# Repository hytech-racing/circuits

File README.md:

# circuits
Circuit design for the 2015-2016 car
## Getting Started
1. Get access to Google Drive folder
2. Download [Eagle CAD](http://www.cadsoftusa.com/download-eagle/)
3. Download vehicle electrical diagram from Google Drive: ***Hytech Main Folder/Subteam Files/Electrical/Wiring Diagram/***
4. Download EAGLE Hytech library from Google Drive: ***Hytech Main Folder/Subteam Files/Electrical/HyTech 2016.lbr***

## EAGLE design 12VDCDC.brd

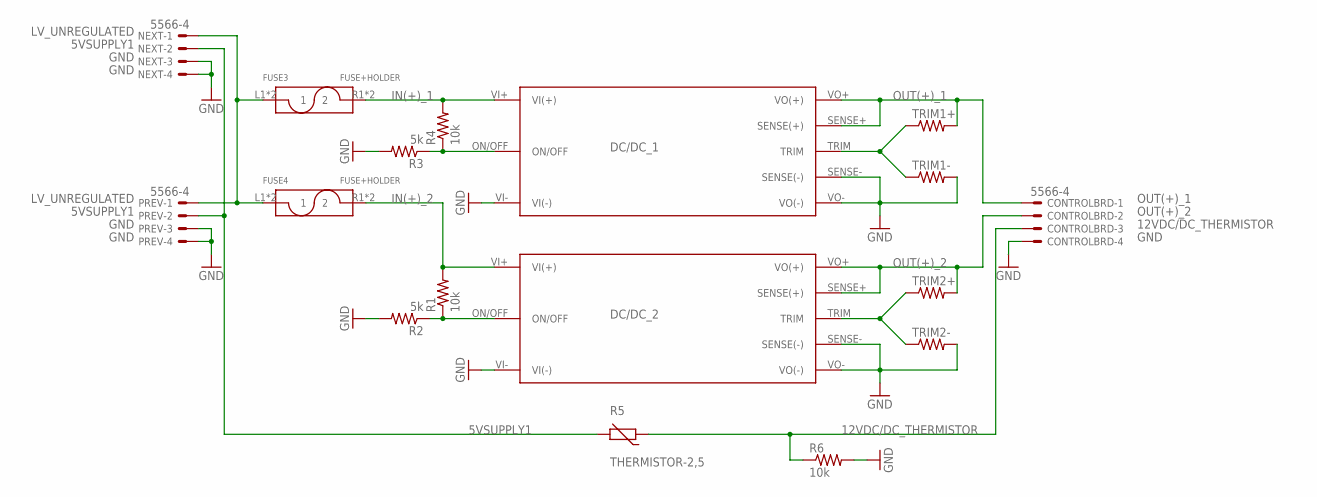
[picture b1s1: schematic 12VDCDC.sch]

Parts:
CONTROLBRD: 5566-4
DC/DC_1, DC/DC_2: DC/DC-EIGHTH_BRICKEHHD006A0B41-HZ; DC/DC-EIGHTH_BRICK
FUSE3, FUSE4: FUSE+HOLDER; FUSE-HOLDER
NEXT: 5566-4
PREV: 5566-4
R1, R4, R6: 10k; AXIAL-0.3
R2, R3: 5k; AXIAL-0.3
R5: THERMISTOR-2,5; RS-2,5
TRIM1+, TRIM1-, TRIM2+, TRIM2-: RESISTORPTH-1/4W; AXIAL-0.4

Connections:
5VSUPPLY1: NEXT.2, PREV.2, R5.2
12VDC/DC_THERMISTOR: CONTROLBRD.3, R5.1, R6.P$1 (1)
GND: CONTROLBRD.4, DC/DC_1.SENSE- (SENSE(-)), DC/DC_1.VI- (VI(-)), DC/DC_1.VO- (VO(-)), DC/DC_2.SENSE- (SENSE(-)), DC/DC_2.VI- (VI(-)), DC/DC_2.VO- (VO(-)), NEXT.3, NEXT.4, PREV.3, PREV.4, R2.P$2 (2), R3.P$2 (2), R6.P$2 (2), TRIM1-.P$2 (2), TRIM2-.P$2 (2)
IN(+)_1: DC/DC_1.VI+ (VI(+)), FUSE3.R1 (2), FUSE3.R2 (2), R4.P$2 (2)
IN(+)_2: DC/DC_2.VI+ (VI(+)), FUSE4.R1 (2), FUSE4.R2 (2), R1.P$2 (2)
LV_UNREGULATED: FUSE3.L1 (1), FUSE3.L2 (1), FUSE4.L1 (1), FUSE4.L2 (1), NEXT.1, PREV.1
unnamed: DC/DC_1.TRIM, TRIM1+.P$1 (1), TRIM1-.P$1 (1)
unnamed: DC/DC_2.ON/OFF, R1.P$1 (1), R2.P$1 (1)
unnamed: DC/DC_1.ON/OFF, R3.P$1 (1), R4.P$1 (1)
unnamed: DC/DC_2.TRIM, TRIM2+.P$1 (1), TRIM2-.P$1 (1)
OUT(+)_1: CONTROLBRD.1, DC/DC_1.SENSE+ (SENSE(+)), DC/DC_1.VO+ (VO(+)), TRIM1+.P$2 (2)
OUT(+)_2: CONTROLBRD.2, DC/DC_2.SENSE+ (SENSE(+)), DC/DC_2.VO+ (VO(+)), TRIM2+.P$2 (2)

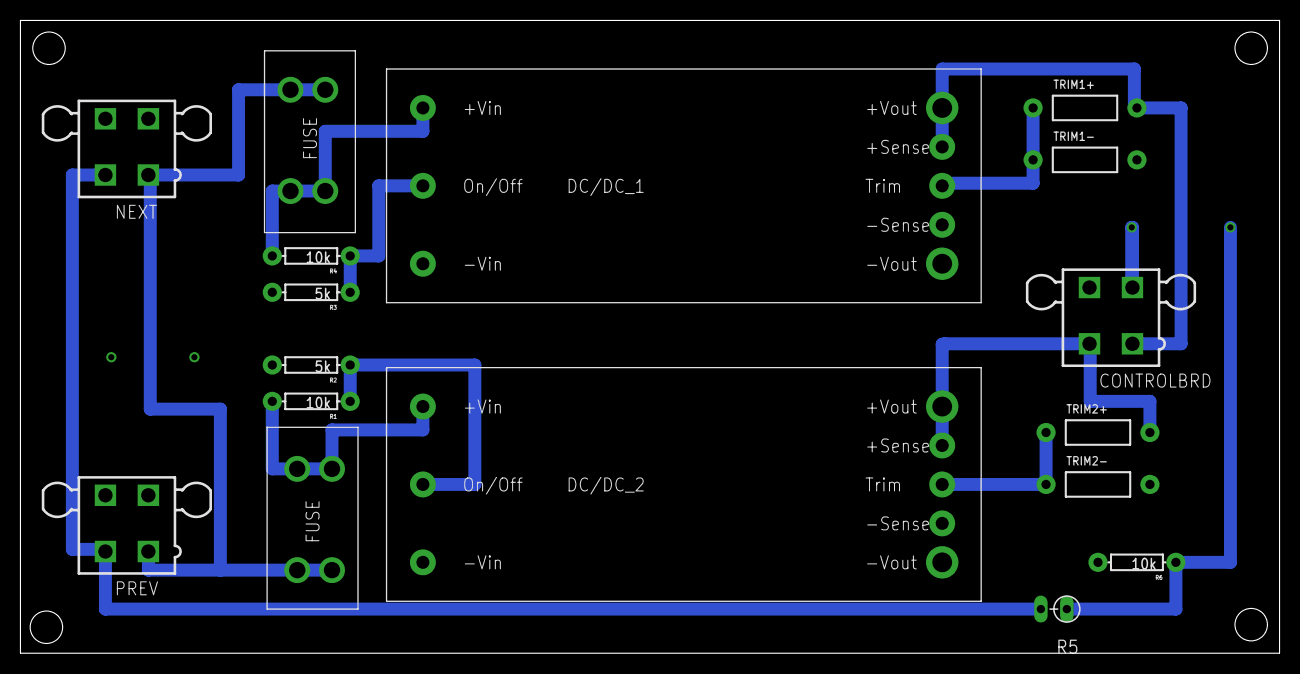
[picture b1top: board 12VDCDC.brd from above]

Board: 2 copper layers, 123.2 x 61.9 mm, 17 parts (0 on the bottom side), 12 nets.

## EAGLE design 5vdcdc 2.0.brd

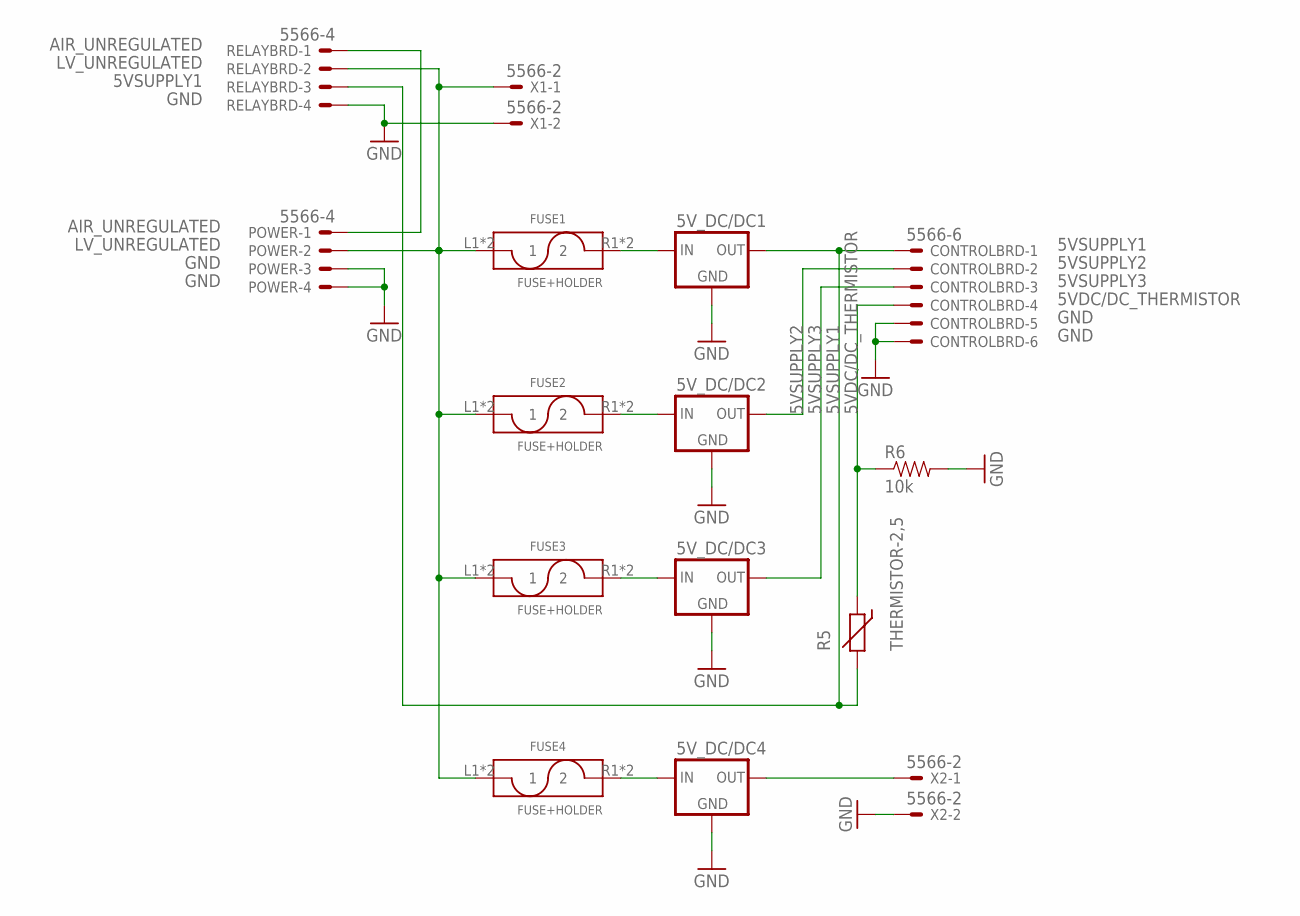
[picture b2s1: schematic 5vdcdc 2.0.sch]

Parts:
5V_DC/DC1, 5V_DC/DC2, 5V_DC/DC3, 5V_DC/DC4: 5V_REGULATORLINEAR; TO-220-SINK
CONTROLBRD: 5566-6
FUSE1, FUSE2, FUSE3, FUSE4: FUSE+HOLDER; FUSE-HOLDER
POWER: 5566-4
R5: THERMISTOR-2,5; RS-2,5
R6: 10k; AXIAL-0.3
RELAYBRD: 5566-4
X1, X2: 5566-2

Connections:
5VDC/DC_THERMISTOR: CONTROLBRD.4, R5.1, R6.P$1 (1)
5VSUPPLY1: 5V_DC/DC1.3 (OUT), CONTROLBRD.1, R5.2, RELAYBRD.3
5VSUPPLY2: 5V_DC/DC2.3 (OUT), CONTROLBRD.2
5VSUPPLY3: 5V_DC/DC3.3 (OUT), CONTROLBRD.3
AIR_UNREGULATED: POWER.1, RELAYBRD.1
GND: 5V_DC/DC1.2 (GND), 5V_DC/DC2.2 (GND), 5V_DC/DC3.2 (GND), 5V_DC/DC4.2 (GND), CONTROLBRD.5, CONTROLBRD.6, POWER.3, POWER.4, R6.P$2 (2), RELAYBRD.4, X1.2, X2.2
LV_UNREGULATED: FUSE1.L1 (1), FUSE1.L2 (1), FUSE2.L1 (1), FUSE2.L2 (1), FUSE3.L1 (1), FUSE3.L2 (1), FUSE4.L1 (1), FUSE4.L2 (1), POWER.2, RELAYBRD.2, X1.1
unnamed: 5V_DC/DC1.1 (IN), FUSE1.R1 (2), FUSE1.R2 (2)
unnamed: 5V_DC/DC2.1 (IN), FUSE2.R1 (2), FUSE2.R2 (2)
unnamed: 5V_DC/DC3.1 (IN), FUSE3.R1 (2), FUSE3.R2 (2)
unnamed: 5V_DC/DC4.1 (IN), FUSE4.R1 (2), FUSE4.R2 (2)
unnamed: 5V_DC/DC4.3 (OUT), X2.1

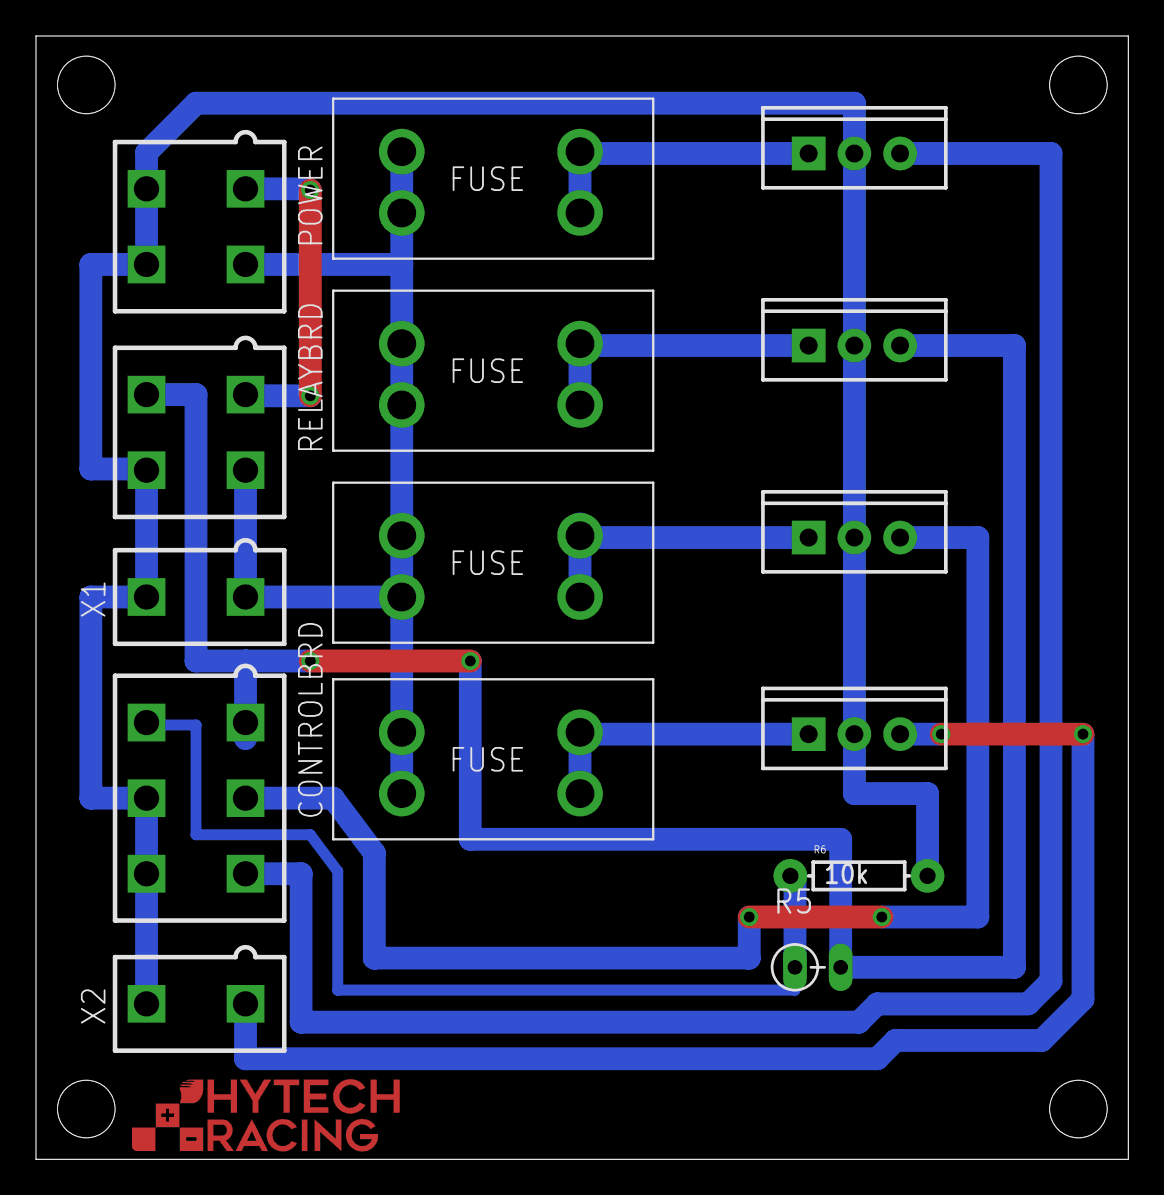
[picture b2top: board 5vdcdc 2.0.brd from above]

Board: 2 copper layers, 60.7 x 62.4 mm, 15 parts (0 on the bottom side), 12 nets.

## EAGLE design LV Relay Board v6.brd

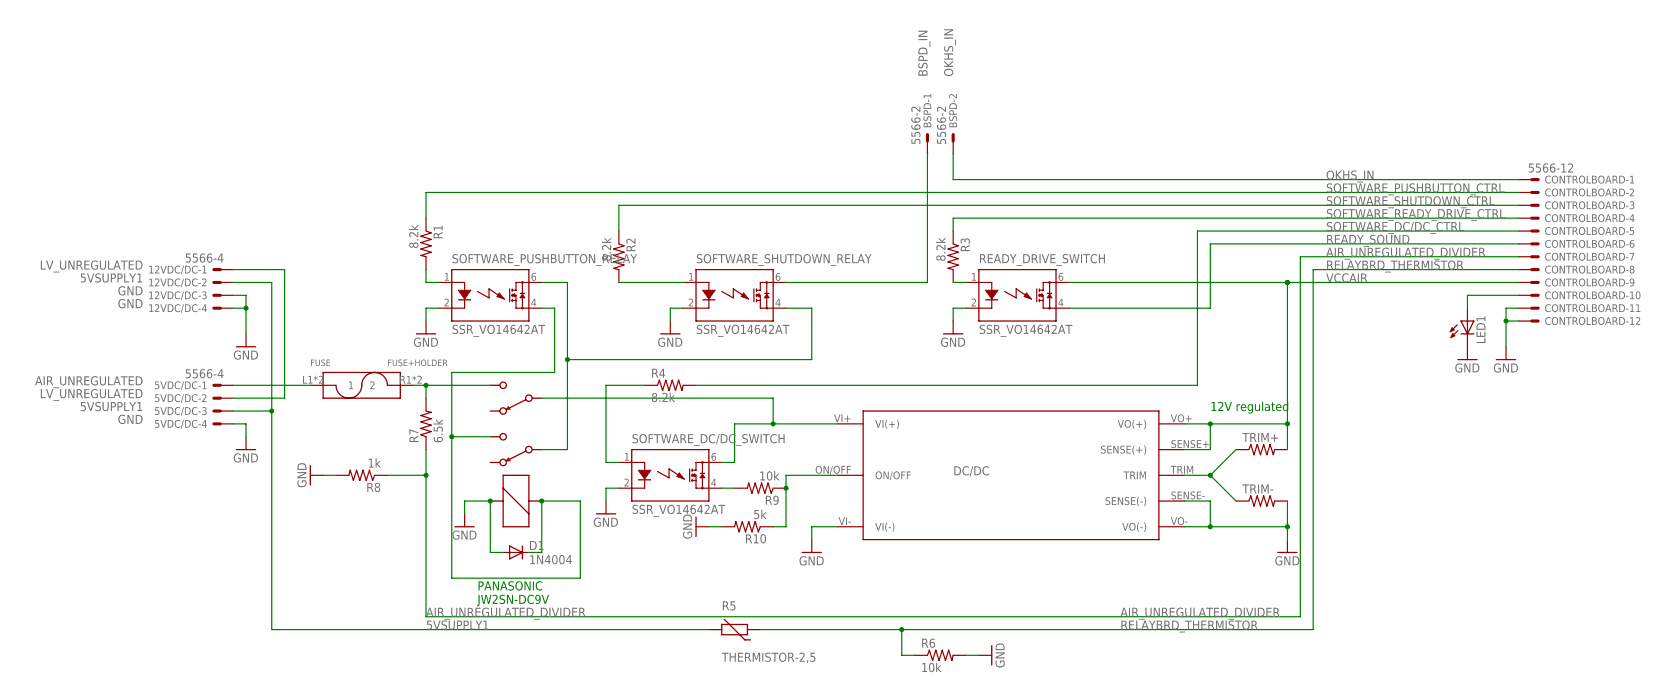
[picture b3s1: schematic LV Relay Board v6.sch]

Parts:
5VDC/DC, 12VDC/DC: 5566-4
BSPD: 5566-2
CONTROLBOARD: 5566-12
D1: 1N4004; DO41-10
DC/DC: DC/DC-EIGHTH_BRICKUWE-12/10-Q12PB-C; DC/DC-EIGHTH_BRICK
FUSE: FUSE+HOLDER; FUSE-HOLDER
LED1: LED3MM
PANASONIC_JW2SN-DC9V_RELAY: PANASONIC_JW2SN-DC9V_RELAY
R1, R2, R3, R4: 8.2k; AXIAL-0.4
R5: THERMISTOR-2,5; RS-2,5
R6, R9: 10k; AXIAL-0.4
R7: 6.5k; AXIAL-0.4
R8: 1k; AXIAL-0.4
R10: 5k; AXIAL-0.4
READY_DRIVE_SWITCH: SSR_VO14642AT; DIL06
SOFTWARE_DC/DC_SWITCH: SSR_VO14642AT; DIL06
SOFTWARE_PUSHBUTTON_RELAY: SSR_VO14642AT; DIL06
SOFTWARE_SHUTDOWN_RELAY: SSR_VO14642AT; DIL06
TRIM+: RESISTORPTH-1/4W; AXIAL-0.4
TRIM-: RESISTORPTH-1/4W; AXIAL-0.4

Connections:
5VSUPPLY1: 5VDC/DC.3, 12VDC/DC.2, R5.2
AIR_UNREGULATED: 5VDC/DC.1, FUSE.L1 (1), FUSE.L2 (1)
AIR_UNREGULATED_DIVIDER: CONTROLBOARD.7, R7.P$1 (1), R8.P$1 (1)
BSPD_IN: BSPD.1, SOFTWARE_SHUTDOWN_RELAY.6 (IO1)
GND: 5VDC/DC.4, 12VDC/DC.3, 12VDC/DC.4, CONTROLBOARD.11, CONTROLBOARD.12, D1.A, DC/DC.SENSE- (SENSE(-)), DC/DC.VI- (VI(-)), DC/DC.VO- (VO(-)), LED1.K (C), PANASONIC_JW2SN-DC9V_RELAY.COIL+, R6.P$2 (2), R8.P$2 (2), R10.P$2 (2), READY_DRIVE_SWITCH.2 (LED-), SOFTWARE_DC/DC_SWITCH.2 (LED-), SOFTWARE_PUSHBUTTON_RELAY.2 (LED-), SOFTWARE_SHUTDOWN_RELAY.2 (LED-), TRIM-.P$2 (2)
LV_UNREGULATED: 5VDC/DC.2, 12VDC/DC.1
unnamed: R9.P$2 (2), SOFTWARE_DC/DC_SWITCH.4 (IO2)
unnamed: DC/DC.VI+ (VI(+)), PANASONIC_JW2SN-DC9V_RELAY.6, SOFTWARE_DC/DC_SWITCH.6 (IO1)
unnamed: FUSE.R1 (2), FUSE.R2 (2), PANASONIC_JW2SN-DC9V_RELAY.5, R7.P$2 (2)
unnamed: PANASONIC_JW2SN-DC9V_RELAY.3, SOFTWARE_PUSHBUTTON_RELAY.6 (IO1), SOFTWARE_SHUTDOWN_RELAY.4 (IO2)
unnamed: R1.P$2 (2), SOFTWARE_PUSHBUTTON_RELAY.1 (LED+)
unnamed: D1.C, PANASONIC_JW2SN-DC9V_RELAY.4, PANASONIC_JW2SN-DC9V_RELAY.COIL-, SOFTWARE_PUSHBUTTON_RELAY.4 (IO2)
unnamed: R2.P$2 (2), SOFTWARE_SHUTDOWN_RELAY.1 (LED+)
unnamed: DC/DC.TRIM, TRIM+.P$1 (1), TRIM-.P$1 (1)
unnamed: R3.P$2 (2), READY_DRIVE_SWITCH.1 (LED+)
unnamed: R4.P$1 (1), SOFTWARE_DC/DC_SWITCH.1 (LED+)
unnamed: DC/DC.ON/OFF, R9.P$1 (1), R10.P$1 (1)
unnamed: CONTROLBOARD.10, LED1.A
OKHS_IN: BSPD.2, CONTROLBOARD.1
READY_SOUND: CONTROLBOARD.6, READY_DRIVE_SWITCH.4 (IO2)
RELAYBRD_THERMISTOR: CONTROLBOARD.8, R5.1, R6.P$1 (1)
SOFTWARE_DC/DC_CTRL: CONTROLBOARD.5, R4.P$2 (2)
SOFTWARE_PUSHBUTTON_CTRL: CONTROLBOARD.2, R1.P$1 (1)
SOFTWARE_READY_DRIVE_CTRL: CONTROLBOARD.4, R3.P$1 (1)
SOFTWARE_SHUTDOWN_CTRL: CONTROLBOARD.3, R2.P$1 (1)
VCCAIR: CONTROLBOARD.9, DC/DC.SENSE+ (SENSE(+)), DC/DC.VO+ (VO(+)), READY_DRIVE_SWITCH.6 (IO1), TRIM+.P$2 (2)

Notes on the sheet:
PANASONIC JW2SN-DC9V
12V regulated

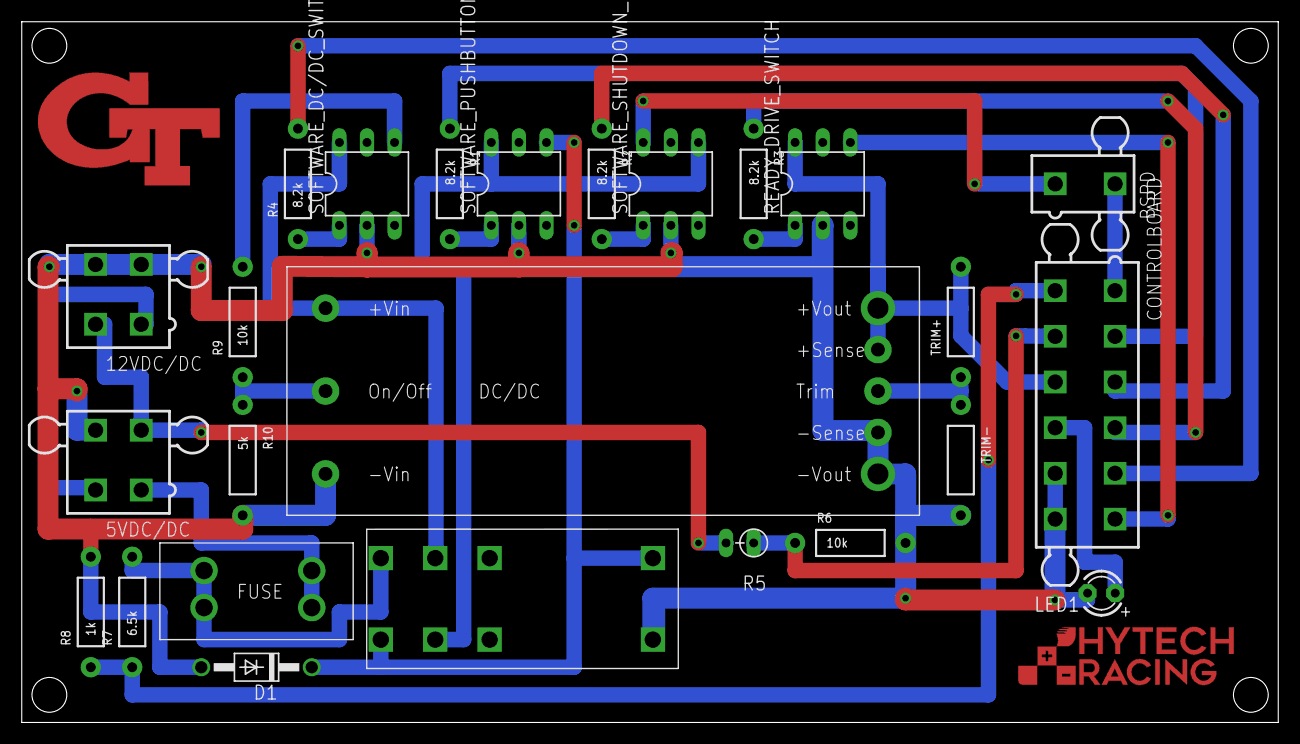
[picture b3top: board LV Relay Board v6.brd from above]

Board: 2 copper layers, 115.5 x 64.4 mm, 25 parts (0 on the bottom side), 26 nets.

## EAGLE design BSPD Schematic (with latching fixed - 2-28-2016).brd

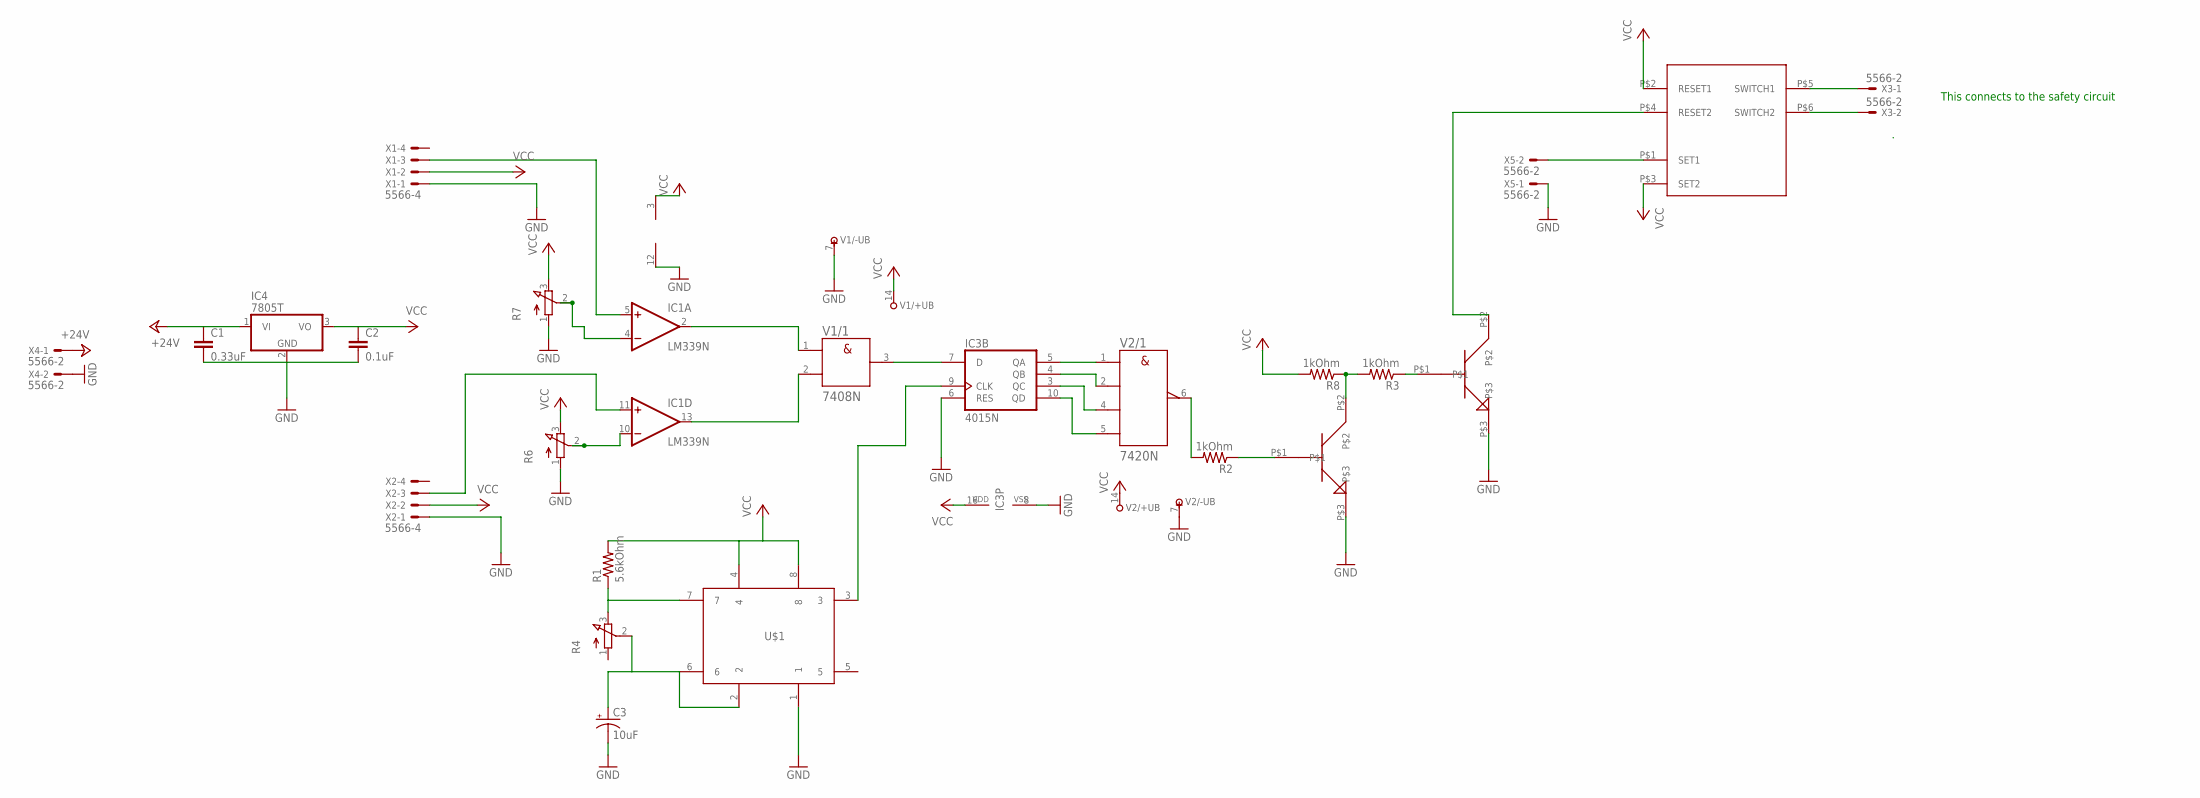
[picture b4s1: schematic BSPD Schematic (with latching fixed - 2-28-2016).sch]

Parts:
C1: 0.33uF; CAP-PTH-LARGE
C2: 0.1uF; CAP-PTH-LARGE
C3: 10uF; E2,5-7
IC1: LM339N; DIL14
IC3: 4015N; DIL16
IC4: 7805T; TO220H
R1: 5.6kOhm; 1/6W-RES
R2, R3, R8: 1kOhm; 1/6W-RES
R4, R6, R7: 3RP/1610N
U$1: 555_TIMER555_TIMER; DIL08
U$2, U$4: TRANSISTOR_ZTX653THROUGH_HOLE; TRANSISTOR
U$3: LATCHING_RELAY_G6CK-1117P-US-DC5
V1: 7408N; DIL14
V2: 7420N; DIL14
X1, X2: 5566-4
X3, X4, X5: 5566-2

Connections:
+24V: C1.1, IC4.1 (VI), X4.1
GND: C1.2, C2.2, C3.-, IC1.12 (GND), IC3.6 (RES), IC3.8 (VSS), IC4.2 (GND), R6.1 (A), R7.1 (A), U$1.1, U$2.P$3, U$4.P$3, V1.7 (-UB), V2.7 (-UB), X1.1, X2.1, X4.2, X5.1
unnamed: IC3.7 (D), V1.3 (Y)
unnamed: R2.2, V2.6 (Y)
unnamed: IC3.4 (QB), V2.2 (B)
unnamed: IC3.3 (QC), V2.4 (C)
unnamed: IC3.10 (QD), V2.5 (D)
unnamed: IC1.13 (OUT), V1.2 (B)
unnamed: IC1.2 (OUT), V1.1 (A)
unnamed: IC3.9 (CLK), U$1.3
unnamed: IC1.10 (-IN), R6.2 (S)
unnamed: IC1.4 (-IN), R7.2 (S)
unnamed: C3.+, R4.2 (S), U$1.2, U$1.6
unnamed: R1.1, R4.3 (E), U$1.7
unnamed: U$3.P$1 (SET1), X5.2
unnamed: U$3.P$5 (SWITCH1), X3.1
unnamed: U$3.P$6 (SWITCH2), X3.2
unnamed: IC3.5 (QA), V2.1 (A)
unnamed: IC1.11 (+IN), X2.3
unnamed: IC1.5 (+IN), X1.3
unnamed: R2.1, U$2.P$1
unnamed: R3.1, U$4.P$1
unnamed: R3.2, R8.1, U$2.P$2
unnamed: U$3.P$4 (RESET2), U$4.P$2
VCC: C2.1, IC1.3 (V+), IC3.16 (VDD), IC4.3 (VO), R1.2, R6.3 (E), R7.3 (E), R8.2, U$1.4, U$1.8, U$3.P$2 (RESET1), U$3.P$3 (SET2), V1.14 (+UB), V2.14 (+UB), X1.2, X2.2

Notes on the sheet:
This connects to the safety circuit

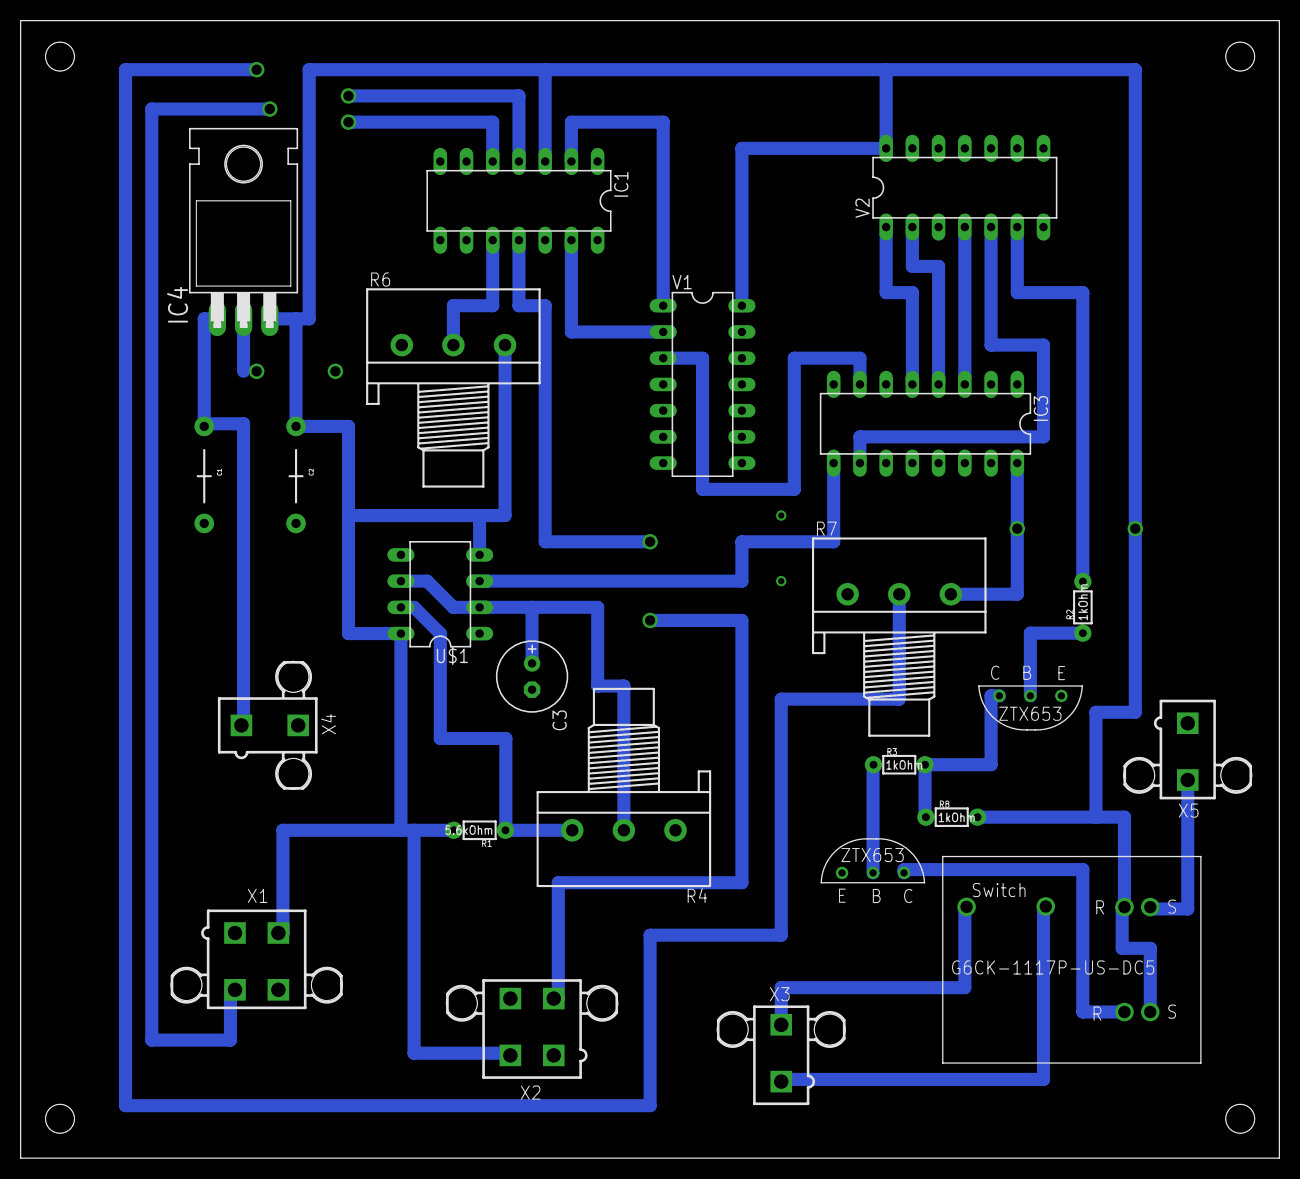
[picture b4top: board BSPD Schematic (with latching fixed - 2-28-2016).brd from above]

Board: 2 copper layers, 121.9 x 110.2 mm, 24 parts (0 on the bottom side), 25 nets.

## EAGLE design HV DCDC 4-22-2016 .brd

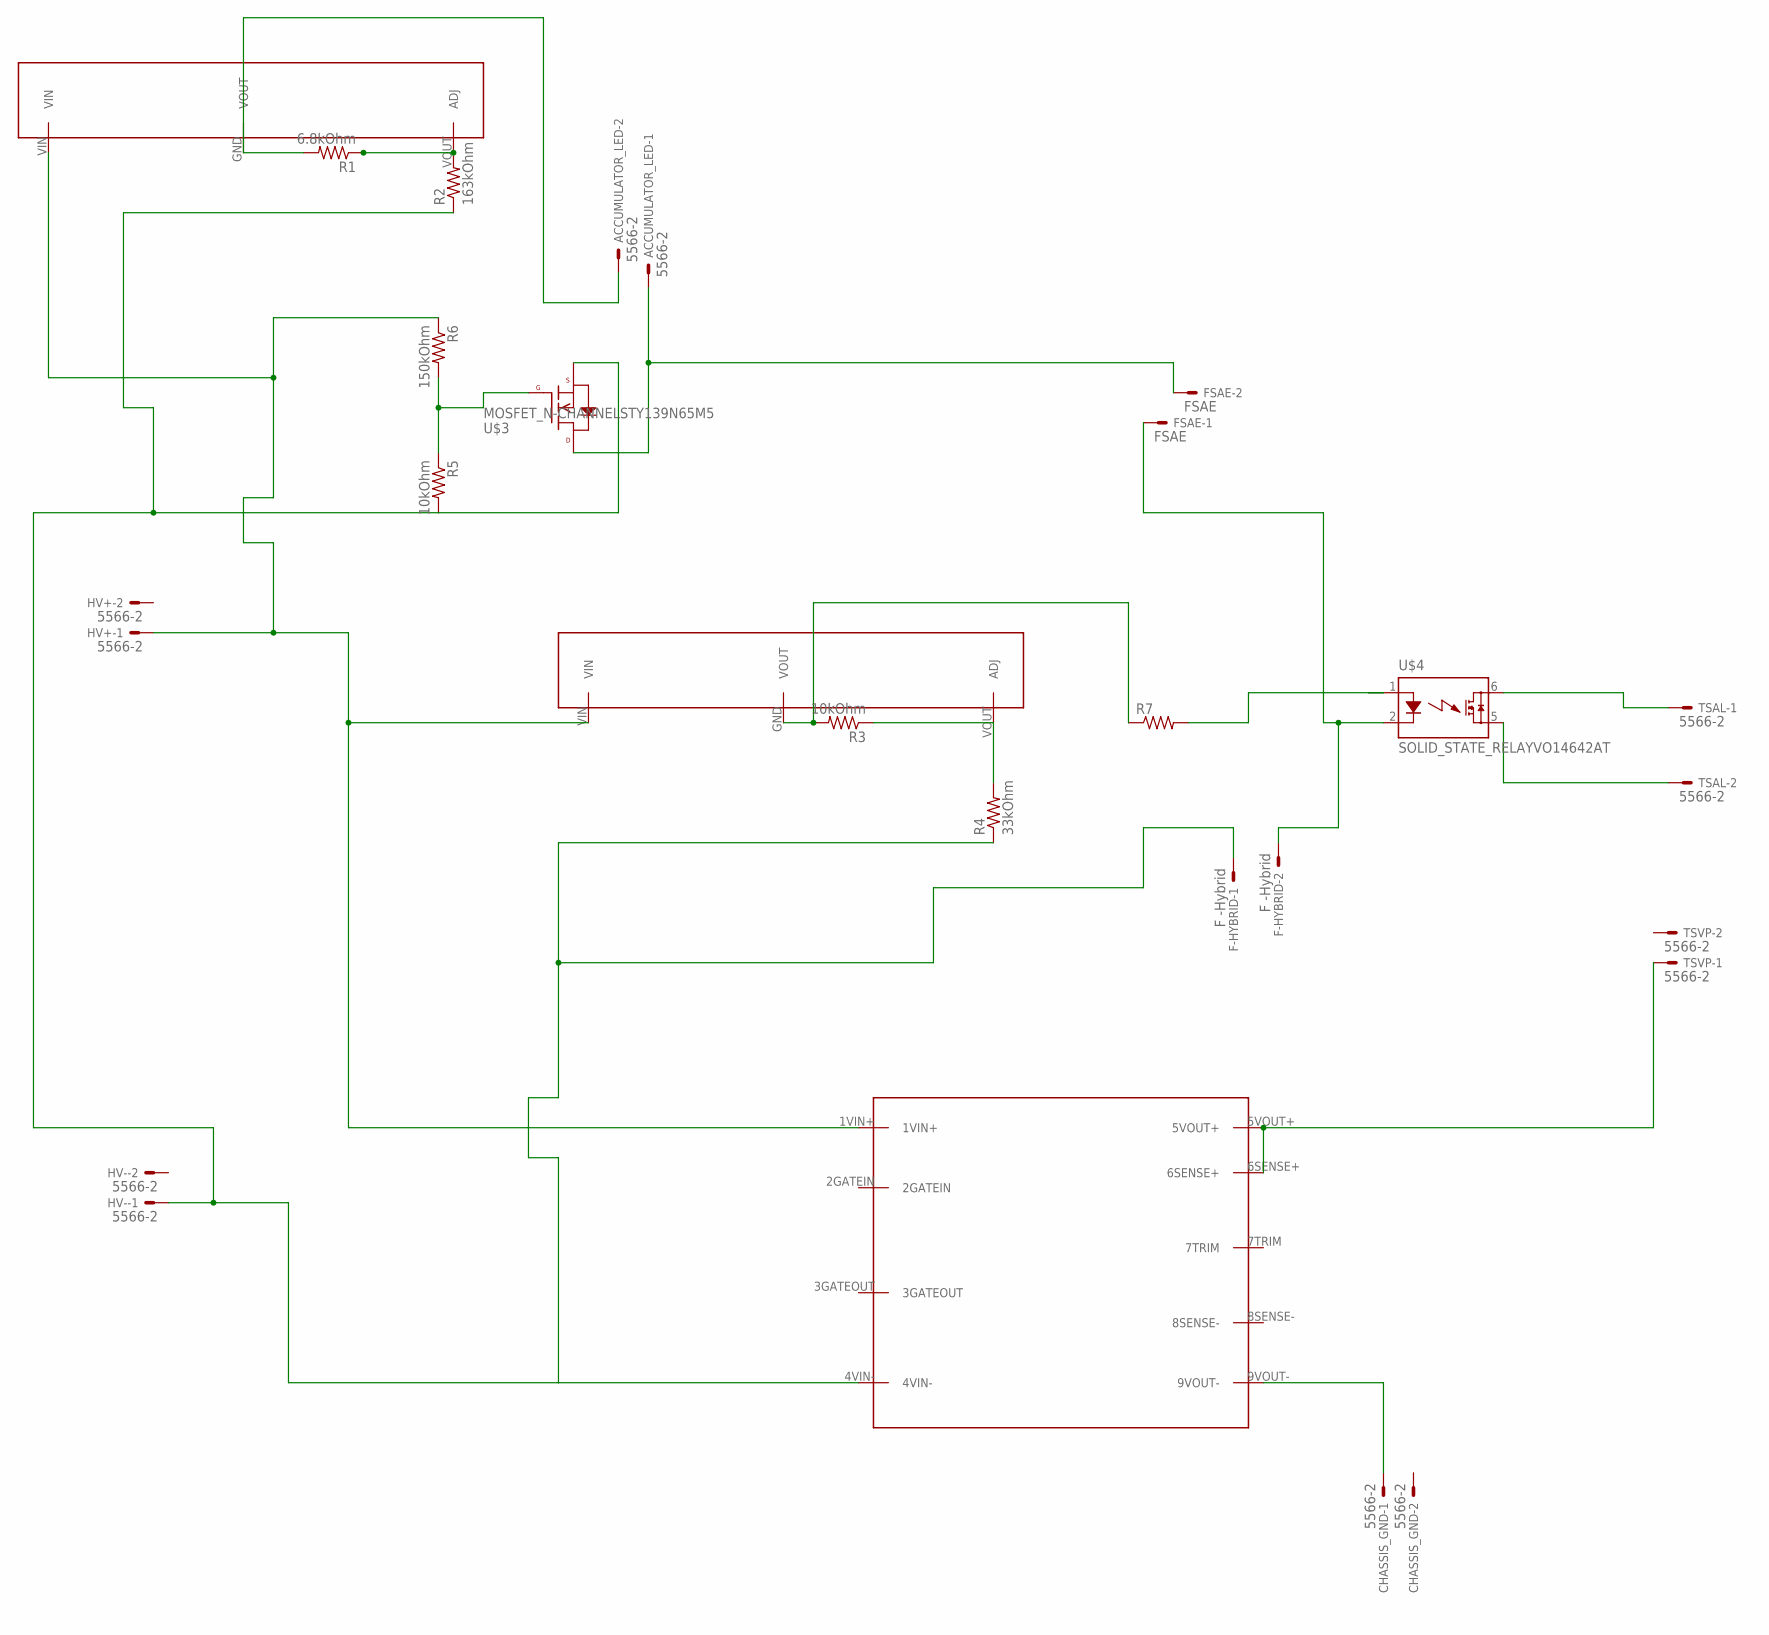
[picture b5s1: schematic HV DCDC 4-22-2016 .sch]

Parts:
ACCUMULATOR_LED: 5566-2
CHASSIS_GND: 5566-2
F-HYBRID: F -Hybrid; 5566-2
FSAE: FSAE; 5566-2
HV+: 5566-2
HV-: 5566-2
R1: 6.8kOhm; AXIAL-0.3
R2: 163kOhm; AXIAL-0.3
R3, R5: 10kOhm; AXIAL-0.3
R4: 33kOhm; AXIAL-0.3
R6: 150kOhm; AXIAL-0.3
R7: RESISTORAXIAL-0.3; AXIAL-0.3
TSAL: 5566-2
TSVP: 5566-2
U$3: MOSFET_N-CHANNELSTY139N65M5; TO-264_MAX247
U$4: SOLID_STATE_RELAYVO14642AT; DIL06
U$5: HV_DCDC_NEW
U$6, U$7: HV_LIN_REG; HV_LIN_REG14MM

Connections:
unnamed: TSAL.1, U$4.6 (IO1)
unnamed: ACCUMULATOR_LED.1, FSAE.2, U$3.P2 (DRAIN)
unnamed: HV+.1, R6.P$1 (1), U$5.1VIN+, U$6.VIN, U$7.VIN
unnamed: R5.P$1 (1), R6.P$2 (2), U$3.P1 (GATE)
unnamed: F-HYBRID.2, FSAE.1, U$4.2 (LED-)
unnamed: R3.P$2 (2), R7.P$1 (1), U$6.GND (VOUT)
unnamed: R3.P$1 (1), R4.P$2 (2), U$6.VOUT (ADJ)
unnamed: F-HYBRID.1, HV-.1, R2.P$1 (1), R4.P$1 (1), R5.P$2 (2), U$3.P3 (SOURCE), U$5.4VIN-
unnamed: TSAL.2, U$4.5 (IO2)
unnamed: TSVP.1, U$5.5VOUT+, U$5.6SENSE+
unnamed: R1.P$1 (1), R2.P$2 (2), U$7.VOUT (ADJ)
unnamed: ACCUMULATOR_LED.2, R1.P$2 (2), U$7.GND (VOUT)
unnamed: CHASSIS_GND.1, U$5.9VOUT-
unnamed: R7.P$2 (2), U$4.1 (LED+)

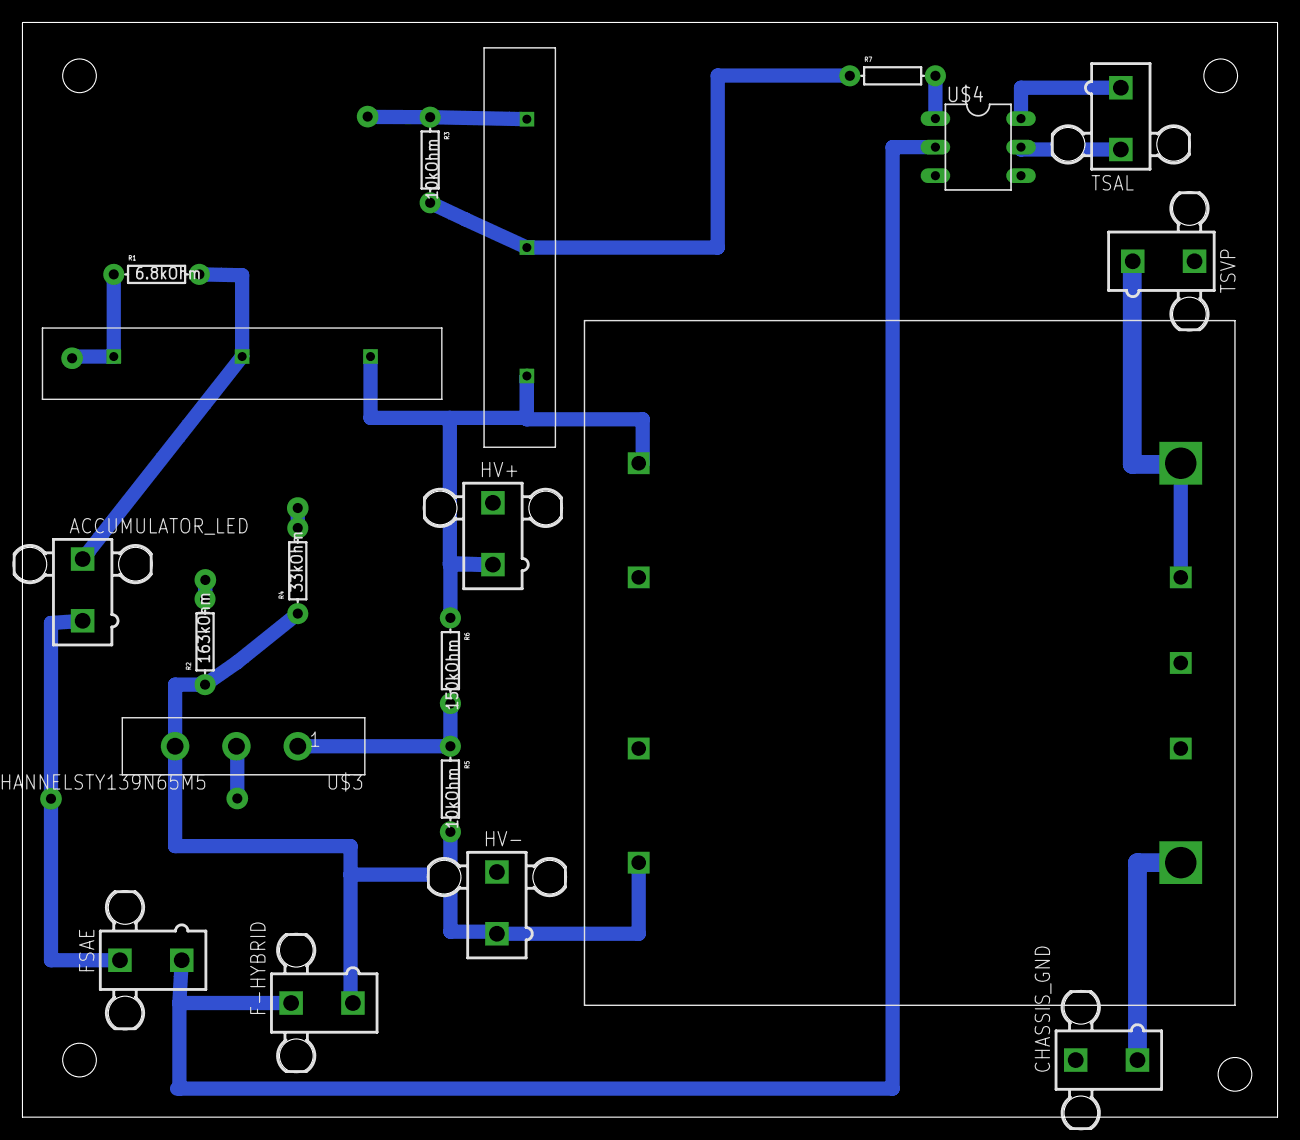
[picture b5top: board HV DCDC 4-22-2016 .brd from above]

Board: 2 copper layers, 111.7 x 97.5 mm, 20 parts (0 on the bottom side), 14 nets.

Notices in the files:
parts and their libraries:
SparkFun-AnalogIC: Licensing:Creative Commons ShareAlike 4.0 International - https://creativecommons.org/licenses/by-sa/4.0
